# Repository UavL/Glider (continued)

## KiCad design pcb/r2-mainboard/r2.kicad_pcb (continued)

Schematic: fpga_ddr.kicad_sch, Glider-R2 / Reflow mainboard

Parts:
C800, C801, C804, C810, C811, C812, C813, C814, C815: 470nF/25V; C_0402_1005Metric; MPN CGA0402X5R474K250GT; LCSC C6119801
C802, C803, C805, C806, C807, C808, C809, C819, C820: 100nF/50V; C_0402_1005Metric; MPN CC0402KRX7R9BB104; LCSC C131394
C816, C817, C818: 22uF/6.3V; C_0603_1608Metric; MPN CL10A226MQ8NRNC; LCSC C59461
C821, C822, C823, C824: 22uF/6.3V; C_0603_1608Metric; MPN CL10A226MQ8NRNC
C825, C826, C827, C829, C831, C833: 4.7uF/6.3V; C_0402_1005Metric; MPN CL05A475MQ5NRNC
C828, C830, C832: 470nF/25V; C_0402_1005Metric; MPN CGA0402X5R474K250GT
R800, R806: 100R/1%; R_0402_1005Metric; MPN 0402WGF1000TCE; LCSC C25076
R801, R803, R807: 5.1K/1%; R_0402_1005Metric; MPN 0402WGF5101TCE; LCSC C25905
R802: 240R/1%; R_0402_1005Metric; MPN 0402WGF2400TCE; LCSC C25094
R804, R805: 1K/1%; R_0402_1005Metric; MPN 0402WGF1001TCE; LCSC C11702
U700: XC6SLX-FTG256; Xilinx_FTG256
U800: MT41K64M16TW; BGA-96_9.0x13.0mm_Layout2x3x16_P0.8mm; MPN MT41K64M16TW-107 IT:J; LCSC C524855

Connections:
+1V2_FPGA: C821.1, C823.1, C825.1, C827.1, C829.1, C831.1, C832.1, C833.1, U700.G7 (VCCINT), U700.G9 (VCCINT), U700.H8 (VCCINT), U700.H10 (VCCINT), U700.J7 (VCCINT), U700.J9 (VCCINT), U700.K8 (VCCINT), U700.K10 (VCCINT); also elsewhere on the board
+1V5: C802.1, C803.1, C805.1, C806.1, C808.1, C809.1, C810.1, C811.1, C812.1, C813.1, C814.1, C815.1, C816.1, C817.1, C818.1, C819.1, R804.1, U700.D2 (VCCO_3), U700.G4 (VCCO_3), U700.J2 (VCCO_3), U700.K4 (VCCO_3), U700.N2 (VCCO_3), U800.A1 (VDDQ), U800.A8 (VDDQ), U800.B2 (VDD), U800.C1 (VDDQ), U800.C9 (VDDQ), U800.D2 (VDDQ), U800.D9 (VDD), U800.E9 (VDDQ), U800.F1 (VDDQ), U800.G7 (VDD), U800.H2 (VDDQ), U800.H9 (VDDQ), U800.K2 (VDD), U800.K8 (VDD), U800.N1 (VDD), U800.N9 (VDD), U800.R1 (VDD), U800.R9 (VDD); also elsewhere on the board
+3V3: C822.1, C824.1, C826.1, C828.1, C830.1, U700.E5 (VCCAUX), U700.F8 (VCCAUX), U700.F11 (VCCAUX), U700.G10 (VCCAUX), U700.H6 (VCCAUX), U700.J10 (VCCAUX), U700.L6 (VCCAUX), U700.L9 (VCCAUX); also elsewhere on the board
+DRAM_VREF: C800.1, C801.1, C804.1, C807.1, C819.2, C820.1, R804.2, R805.1, U700.A3 (IO_L83N_VREF_3), U700.M3 (IO_L1N_VREF_3), U800.H1 (VrefDQ), U800.M8 (VrefCA)
/fpga_ddr/DRAM_ADDR0: U700.K5 (IO_L47P_M3A0_3), U800.N3 (A0)
/fpga_ddr/DRAM_ADDR1: U700.K6 (IO_L47N_M3A1_3), U800.P7 (A1)
/fpga_ddr/DRAM_ADDR2: U700.D1 (IO_L49N_M3A2_3), U800.P3 (A2)
/fpga_ddr/DRAM_ADDR3: U700.L4 (IO_L45P_M3A3_3), U800.N2 (A3)
/fpga_ddr/DRAM_ADDR4: U700.G5 (IO_L51N_M3A4_3), U800.P8 (A4)
/fpga_ddr/DRAM_ADDR5: U700.H4 (IO_L44P_GCLK21_M3A5_3), U800.P2 (A5)
/fpga_ddr/DRAM_ADDR6: U700.H3 (IO_L44N_GCLK20_M3A6_3), U800.R8 (A6)
/fpga_ddr/DRAM_ADDR7: U700.D3 (IO_L49P_M3A7_3), U800.R2 (A7)
/fpga_ddr/DRAM_ADDR8: U700.B2 (IO_L52P_M3A8_3), U800.T8 (A8)
/fpga_ddr/DRAM_ADDR9: U700.A2 (IO_L52N_M3A9_3), U800.R3 (A9)
/fpga_ddr/DRAM_ADDR10: U700.G6 (IO_L51P_M3A10_3), U800.L7 (A10)
/fpga_ddr/DRAM_ADDR11: U700.E3 (IO_L54N_M3A11_3), U800.R7 (A11)
/fpga_ddr/DRAM_ADDR12: U700.F3 (IO_L53N_M3A12_3), U800.N7 (A12/~BC)
/fpga_ddr/DRAM_ADDR13: U700.F6 (IO_L55P_M3A13_3), U800.T3 (A13)
/fpga_ddr/DRAM_ADDR14: U700.F5 (IO_L55N_M3A14_3), U800.T7 (A14/NC)
/fpga_ddr/DRAM_BA0: U700.C3 (IO_L48P_M3BA0_3), U800.M2 (BA0)
/fpga_ddr/DRAM_BA1: U700.C2 (IO_L48N_M3BA1_3), U800.N8 (BA1)
/fpga_ddr/DRAM_BA2: U700.B1 (IO_L50N_M3BA2_3), U800.M3 (BA2)
/fpga_ddr/DRAM_CASB: U700.H5 (IO_L43N_GCLK22_IRDY2_M3CASN_3), U800.K3 (~CAS)
/fpga_ddr/DRAM_CKE: R807.1, U700.F4 (IO_L53P_M3CKE_3), U800.K9 (CKE)
/fpga_ddr/DRAM_CKN: R800.1, U700.E1 (IO_L46N_M3CLKN_3), U800.K7 (~CK)
/fpga_ddr/DRAM_CKP: R800.2, U700.E2 (IO_L46P_M3CLK_3), U800.J7 (CK)
/fpga_ddr/DRAM_CSB: R801.1, U800.L2 (~CS)
/fpga_ddr/DRAM_DATA0: U700.K2 (IO_L37P_M3DQ0_3), U800.E3 (DQ0)
/fpga_ddr/DRAM_DATA1: U700.K1 (IO_L37N_M3DQ1_3), U800.F8 (DQ3)
/fpga_ddr/DRAM_DATA2: U700.J3 (IO_L38P_M3DQ2_3), U800.F2 (DQ2)
/fpga_ddr/DRAM_DATA3: U700.J1 (IO_L38N_M3DQ3_3), U800.G2 (DQ6)
/fpga_ddr/DRAM_DATA4: U700.F2 (IO_L41P_GCLK27_M3DQ4_3), U800.H8 (DQ5)
/fpga_ddr/DRAM_DATA5: U700.F1 (IO_L41N_GCLK26_M3DQ5_3), U800.H7 (DQ7)
/fpga_ddr/DRAM_DATA6: U700.G3 (IO_L40P_M3DQ6_3), U800.H3 (DQ4)
/fpga_ddr/DRAM_DATA7: U700.G1 (IO_L40N_M3DQ7_3), U800.F7 (DQ1)
/fpga_ddr/DRAM_DATA8: U700.L3 (IO_L36P_M3DQ8_3), U800.C3 (DQ9)
/fpga_ddr/DRAM_DATA9: U700.L1 (IO_L36N_M3DQ9_3), U800.C2 (DQ11)
/fpga_ddr/DRAM_DATA10: U700.M2 (IO_L35P_M3DQ10_3), U800.A2 (DQ13)
/fpga_ddr/DRAM_DATA11: U700.M1 (IO_L35N_M3DQ11_3), U800.A3 (DQ15)
/fpga_ddr/DRAM_DATA12: U700.P2 (IO_L33P_M3DQ12_3), U800.C8 (DQ10)
/fpga_ddr/DRAM_DATA13: U700.P1 (IO_L33N_M3DQ13_3), U800.D7 (DQ8)
/fpga_ddr/DRAM_DATA14: U700.R2 (IO_L32P_M3DQ14_3), U800.B8 (DQ14)
/fpga_ddr/DRAM_DATA15: U700.R1 (IO_L32N_M3DQ15_3), U800.A7 (DQ12)
/fpga_ddr/DRAM_LDM: U700.J4 (IO_L42N_GCLK24_M3LDM_3), U800.E7 (LDM)
/fpga_ddr/DRAM_LDQSN: U700.H1 (IO_L39N_M3LDQSN_3), U800.G3 (~LDQS)
/fpga_ddr/DRAM_LDQSP: U700.H2 (IO_L39P_M3LDQS_3), U800.F3 (LDQS)
/fpga_ddr/DRAM_ODT: U700.L5 (IO_L45N_M3ODT_3), U800.K1 (ODT)
/fpga_ddr/DRAM_RASB: U700.J6 (IO_L43P_GCLK23_M3RASN_3), U800.J3 (~RAS)
/fpga_ddr/DRAM_RST: R803.1, U700.E4 (IO_L54P_M3RESET_3), U800.T2 (~RESET)
/fpga_ddr/DRAM_UDM: U700.K3 (IO_L42P_GCLK25_TRDY2_M3UDM_3), U800.D3 (UDM)
/fpga_ddr/DRAM_UDQSN: U700.N1 (IO_L34N_M3UDQSN_3), U800.B7 (~UDQS)
/fpga_ddr/DRAM_UDQSP: U700.N3 (IO_L34P_M3UDQS_3), U800.C7 (UDQS)
/fpga_ddr/DRAM_WEB: U700.C1 (IO_L50P_M3WE_3), U800.L3 (~WE)
GND: C800.2, C801.2, C802.2, C803.2, C804.2, C805.2, C806.2, C807.2, C808.2, C809.2, C810.2, C811.2, C812.2, C813.2, C814.2, C815.2, C816.2, C817.2, C818.2, C820.2, C821.2, C822.2, C823.2, C824.2, C825.2, C826.2, C827.2, C828.2, C829.2, C830.2, C831.2, C832.2, C833.2, R801.2, R802.2, R803.2, R805.2, R806.2, R807.2, U700.A1 (GND), U700.A16 (GND), U700.B7 (GND), U700.B11 (GND), U700.D4 (GND), U700.D13 (GND), U700.E9 (GND), U700.G2 (GND), U700.G8 (GND), U700.G15 (GND), U700.H7 (GND), U700.H9 (GND), U700.H12 (GND), U700.J5 (GND), U700.J8 (GND), U700.K7 (GND), U700.K9 (GND), U700.L2 (GND), U700.L15 (GND), U700.M8 (GND), U700.N13 (GND), U700.P3 (GND), U700.R6 (GND), U700.R10 (GND), U700.T1 (GND), U700.T16 (GND), U800.A9 (VSS), U800.B1 (VSSQ), U800.B3 (VSS), U800.B9 (VSSQ), U800.D1 (VSSQ), U800.D8 (VSSQ), U800.E1 (VSS), U800.E2 (VSSQ), U800.E8 (VSSQ), U800.F9 (VSSQ), U800.G1 (VSSQ), U800.G8 (VSS), U800.G9 (VSSQ), U800.J1 (VSS), U800.J2 (VSS), U800.J8 (VSS), U800.J9 (VSS), U800.L1 (VSS), U800.L9 (VSS), U800.M1 (VSS), U800.M9 (VSS), U800.P1 (VSS), U800.P9 (VSS), U800.T1 (VSS), U800.T9 (VSS); also elsewhere on the board
unnamed: R806.1, U700.M4 (IO_L1P_3)
unnamed: R802.1, U800.L8 (ZQ)

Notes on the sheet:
does not bond (Micron 1Gb_DDR3L Rev L Fig 7 p.18) and top.v never drives
FPGA core rails. Unit 6 of U41 is 26 GND + 8 VCCAUX + 8 VCCINT; R1 draws
LVCMOS15 and the rest of the bank SSTL15_II, and DS162 Table 7 specifies
Bank 3 VCCO is 1.5 V, not R1's 1.35 V: the UCF constrains DDR_RESET_N as
DRAM_ADDR13/14 reach U52 balls T3/T7, which the fitted 1 Gb MT41K64M16
select (no DDR_CS_N in constraint.ucf, no such port in top.v).
CAP for DRAM0
DRAM_CSB is tied low by R101 and reaches no FPGA pin: the MCB has no chip
SSTL15 over 1.425-1.575 V only. VREF = R104/R105 = 1.500/2 = 0.750 V.
(DDR_A is [12:0]). Kept routed: T3/T7 are the density-expansion balls, so
a 2 Gb or 4 Gb part stays a gateware-only change.
M5 (DDR_ZIO) is reserved for MCB calibration, not spare -- leave it open.
ZIO
VCCINT
on VCCINT that UG393 Table 2-1 (FTG256 LX16) wants and R1 does not fit.
VCCAUX
it on power.kicad_sch, which in R2 has no FPGA. C509 is the fifth 4.7uF

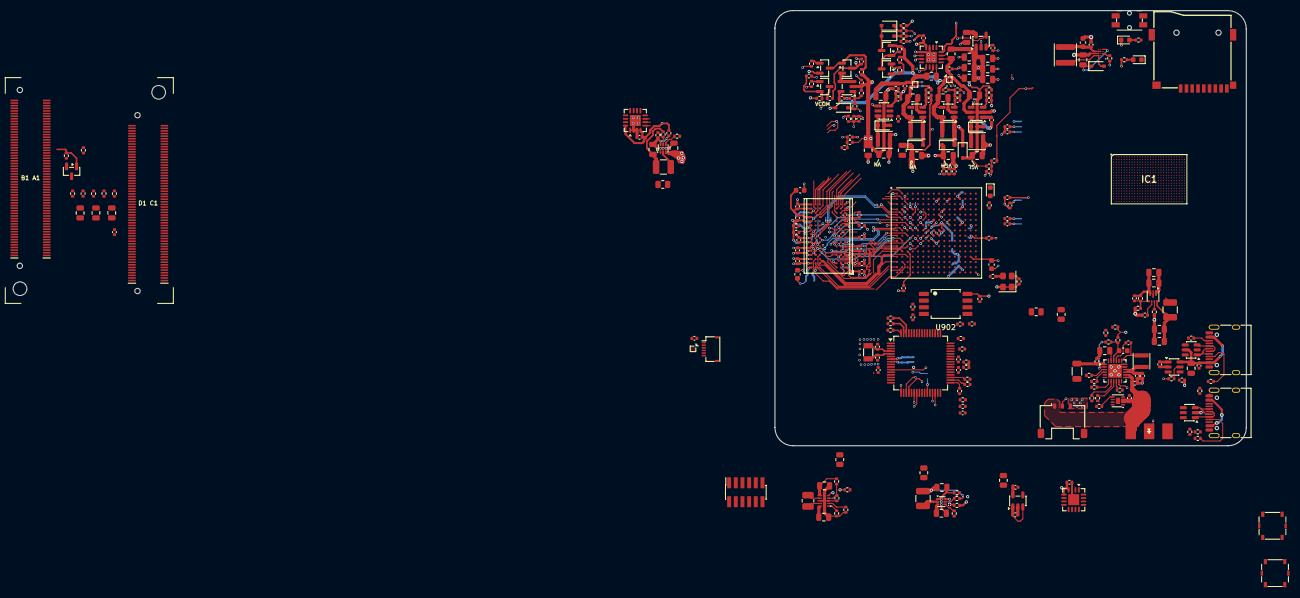
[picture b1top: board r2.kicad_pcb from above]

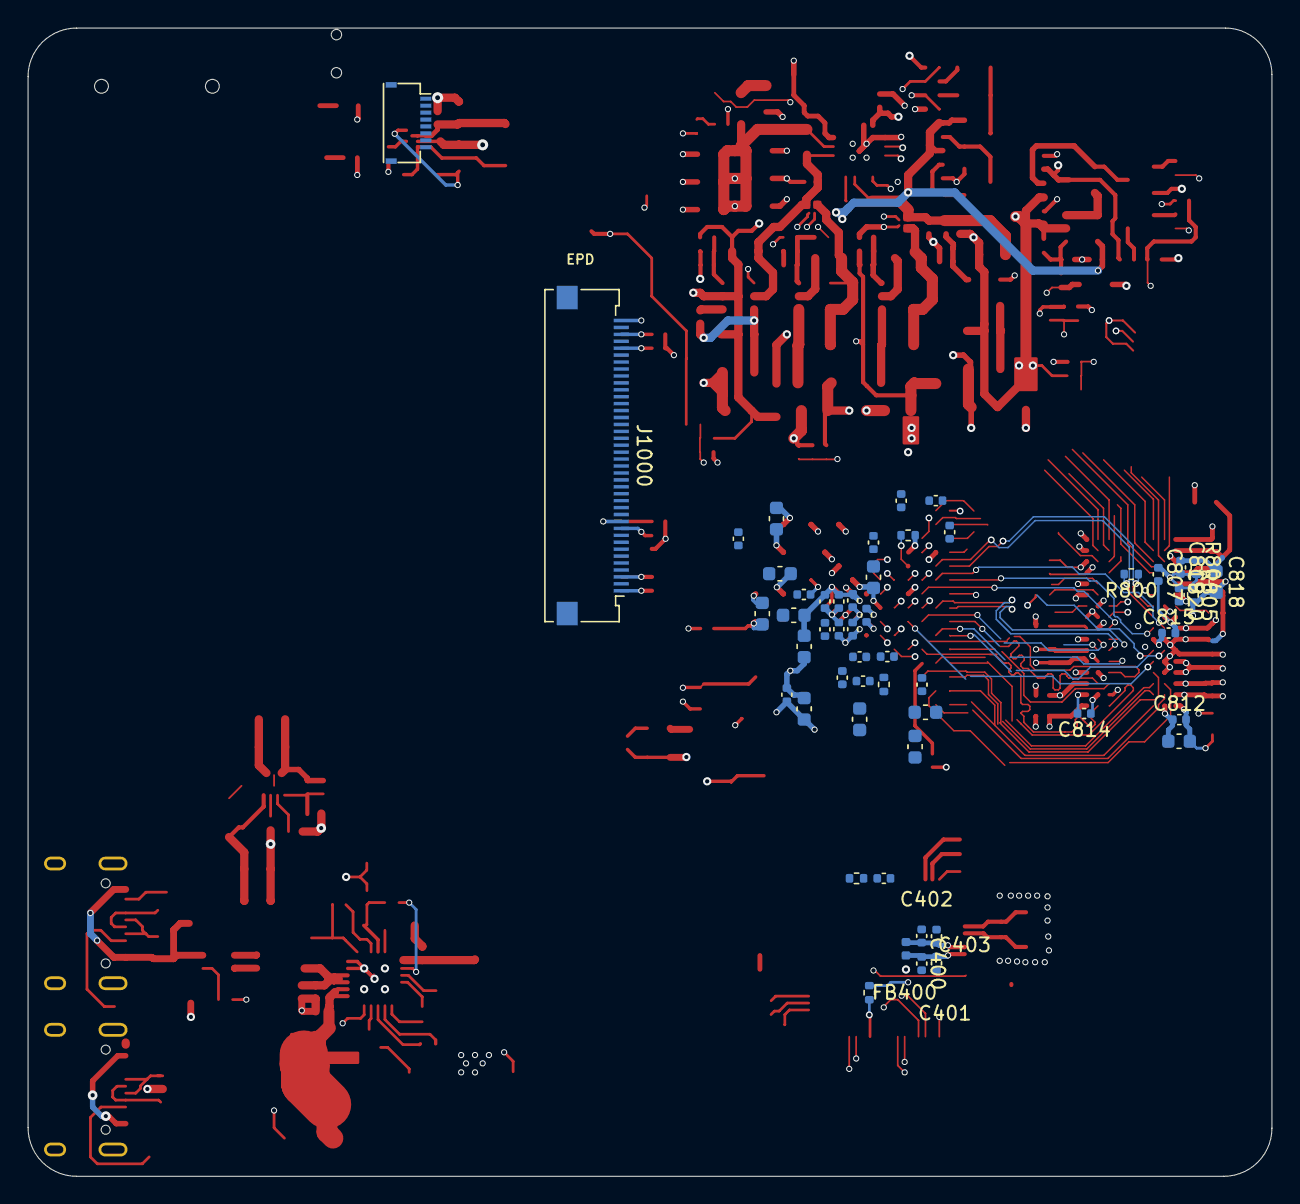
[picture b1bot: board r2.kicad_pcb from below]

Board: 6 copper layers, 89.8 x 82.8 mm, 329 parts (52 on the bottom side), 266 nets.
